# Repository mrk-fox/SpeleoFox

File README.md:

<div align="center">
<h1>SpeleoFox</h1><br>
  
A Speleology headlamp - engineered for the caves 

<br>

<div align="left">v0.1</div>
</div>

SpeleoFox is a DIY helmet-mounted headlamp, designed for caving activities.

> [!WARNING]
> **Early hardware revision.** SpeleoFox has not been manufactured or tested yet. The board is currently waiting on funding before manufacturing.

## Preliminiaries 
Light in caves is more than just an "aid to see". Its a guarantee of surviviability and situation awareness, which results, when abscent, in fatal situations requiring specialised teams for rescue opertions. Caves are natuarally a hostile environment for humans, where moisture and rough, abrasive condition in movement force equipment to reach its limit. Therefore, already since the earliest XXth century, rugged caving and mining headlamps were basic equipment for cavers and miners. Since then LED's (Light Emitting Diodes) reached consumer market electronics making portable light sorces more efficient than ever before. Even though once basic eqipment of some countires 30% of poulation, caving and mining headlams are bound to a high price beginning from 250€. Therefore, this project aimed to create a simple and cheap, yet withstanding, piece of lighting equipment suitable for caving. 

## Features

- Simple, fail-proof electronics
- Modularity and ease of repare
- One led with two lighting modes to cover a variety of situations underground
- Waterproof case
- 2x 18650 Batteries (With protetion!) on the back side of the helmet

## PCB
The PCB features a AMS1117-2.5 controller for the LED intensity regulator and an AL8860 LED Regulator IC

<div align="left">PCB Schematic</div>

<div align="left">PCB Layers</div>

## CAD

The main maxime while designing the CAD for this project was the goal to protect the electronics on the inside from the harsh conditions in the cave. The thorough documentation can be found in the JOURNAL.md file in this repository.

<div align="left">Front (Emitting) Part disassembled</div>

<div align="left">Backside (Battery) Part disassembled</div>

## Assembly

1. First, prepare the PCB by de-panelizing it and soldering all the components according to the BOM, Schematic and PCB Layer (Dont forget to connect the PCBs with a long enoug cable with each other)
2. Print the components in PETG
3. Thermalglue the Radiator to the backside of the LED PCB
4. Place the PCBs into the Printed components
5. Cut a piece of Plexiglass into place and drill holes at the right placec according to the printed part.
6. Use sealant to place the Lids/Plexi onto the 3d printed components after inserting the Batteries
7. Use sealant to seal the cable outlets
8. Screw the components togerther, wait till the sealant dries out and go caving!

## Happy Caving! Please be careful! I thank:
- HACK CLUB
- Kai the Jolly Guy
- Everyone who participated in the 48 hours hackathon!

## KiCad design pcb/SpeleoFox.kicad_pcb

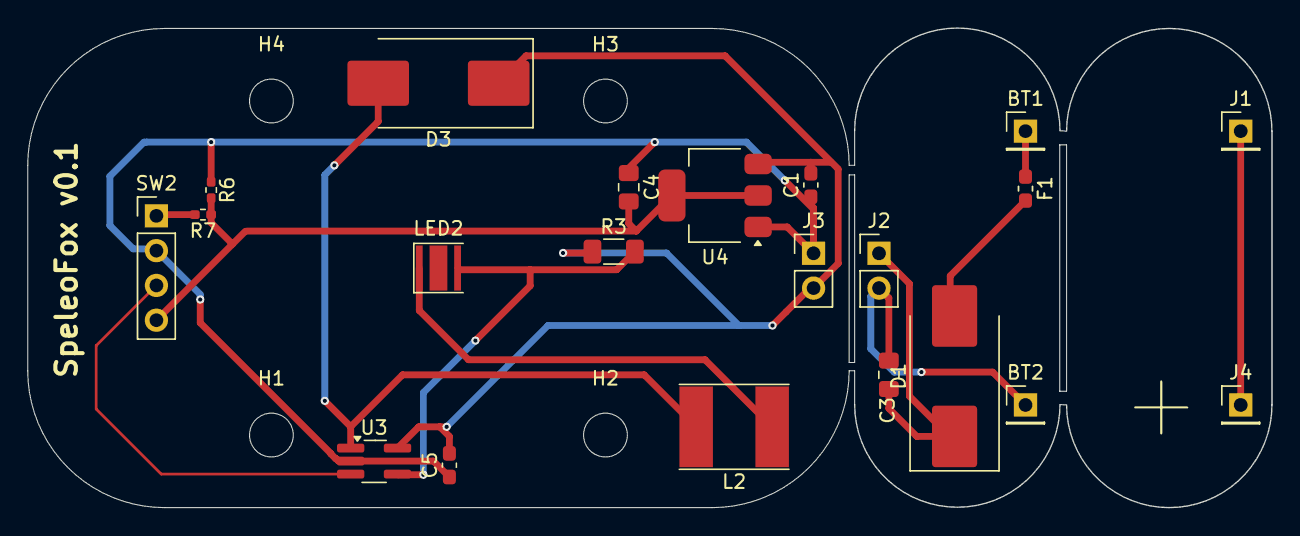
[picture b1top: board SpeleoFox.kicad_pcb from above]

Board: 2 copper layers, 90.9 x 35.0 mm, 25 parts (0 on the bottom side), 13 nets.

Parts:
BT1, BT2: Battery_Cell; PinHeader_1x01_P2.54mm_Vertical
C1, C5: 10µF; C_0603_1608Metric_Pad1.08x0.95mm_HandSolder
C3: 100µF; C_0805_2012Metric_Pad1.18x1.45mm_HandSolder
C4: 22µF; C_0805_2012Metric_Pad1.18x1.45mm_HandSolder
D1, D3: SS34; D_SMC_Handsoldering
F1: 1.5A; Fuse_0603_1608Metric_Pad1.05x0.95mm_HandSolder
H1, H2, H3, H4: MountingHole; MountingHole_3.2mm_M3
J1, J4: Conn_01x01_Pin; PinHeader_1x01_P2.54mm_Vertical
J2: Conn_01x02_Socket; PinHeader_1x02_P2.54mm_Vertical
J3: Conn_01x02_Pin; PinHeader_1x02_P2.54mm_Vertical
L2: 47µH; L_Taiyo-Yuden_NR-60xx_HandSoldering
LED2: Cree_XM-L2_FLOOD; LED_Cree-XP-G
R3: 0.15; R_1206_3216Metric_Pad1.30x1.75mm_HandSolder
R6, R7: 10k; R_0402_1005Metric_Pad0.72x0.64mm_HandSolder
SW2: MODE_ON-ON-ON; PinHeader_1x04_P2.54mm_Vertical
U3: AL8860WT; TSOT-23-5_HandSoldering
U4: AMS1117-2.5; SOT-223-3_TabPin2

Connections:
+2V5: C4.2, R6.2, R7.1, SW2.4, U4.2 (VO)
/CTRL: SW2.3, U3.3 (CTRL)
/VBAT: C1.2, C5.2, D3.1 (K), J3.2, R3.1, U3.5 (VIN), U4.3 (VI)
/VBAT_RAW: BT1.1 (+_1), F1.1
B_GND: BT2.1 (+_1), C3.2, J2.2
GND: C1.1, C4.1, C5.1, J3.1, R6.1, SW2.2, U3.2 (GND), U4.1 (GND)
unnamed: D1.2 (A), F1.2
unnamed: C3.1, D1.1 (K), J2.1
unnamed: D3.2 (A), L2.2, U3.1 (SW)
unnamed: J1.1 (Pin_1_1), J4.1 (Pin_1_1)
unnamed: LED2.2 (A), R3.2, U3.4 (SET)
unnamed: L2.1, LED2.1 (K)
unnamed: R7.2, SW2.1

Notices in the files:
README.md:
License: CERN-OHL-S
